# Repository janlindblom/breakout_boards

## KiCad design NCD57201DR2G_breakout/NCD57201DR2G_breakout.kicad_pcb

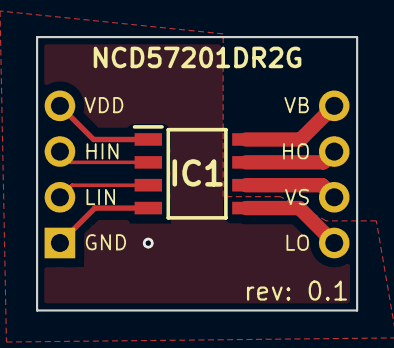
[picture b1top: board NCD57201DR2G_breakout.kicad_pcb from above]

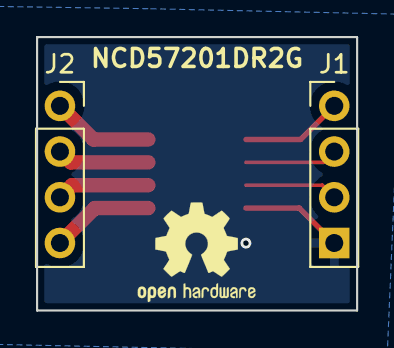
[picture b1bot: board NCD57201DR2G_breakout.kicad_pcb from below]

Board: 2 copper layers, 17.8 x 15.2 mm, 3 parts (2 on the bottom side), 8 nets.

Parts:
IC1: NCD57201DR2G; SOIC127P600X175-8N
J1, J2: Conn_01x04; PinHeader_1x04_P2.54mm_Vertical

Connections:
+5V: IC1.1 (VDD), J1.1
+BATT: IC1.8 (VB), J2.1
-BATT: IC1.6 (VS), J2.3
/HIN: IC1.2 (HIN), J1.2
/HO: IC1.7 (HO), J2.2
/LIN: IC1.3 (LIN), J1.3
/LO: IC1.5 (LO), J2.4
GND1: IC1.4 (GND), J1.4

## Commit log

2024-02-02 Adding .gitignore for KiCad projects.
2024-02-02 Adding NCD57201DR2G breakout board.
2024-02-04 Some updates.
2024-02-08 Pretty much done.
